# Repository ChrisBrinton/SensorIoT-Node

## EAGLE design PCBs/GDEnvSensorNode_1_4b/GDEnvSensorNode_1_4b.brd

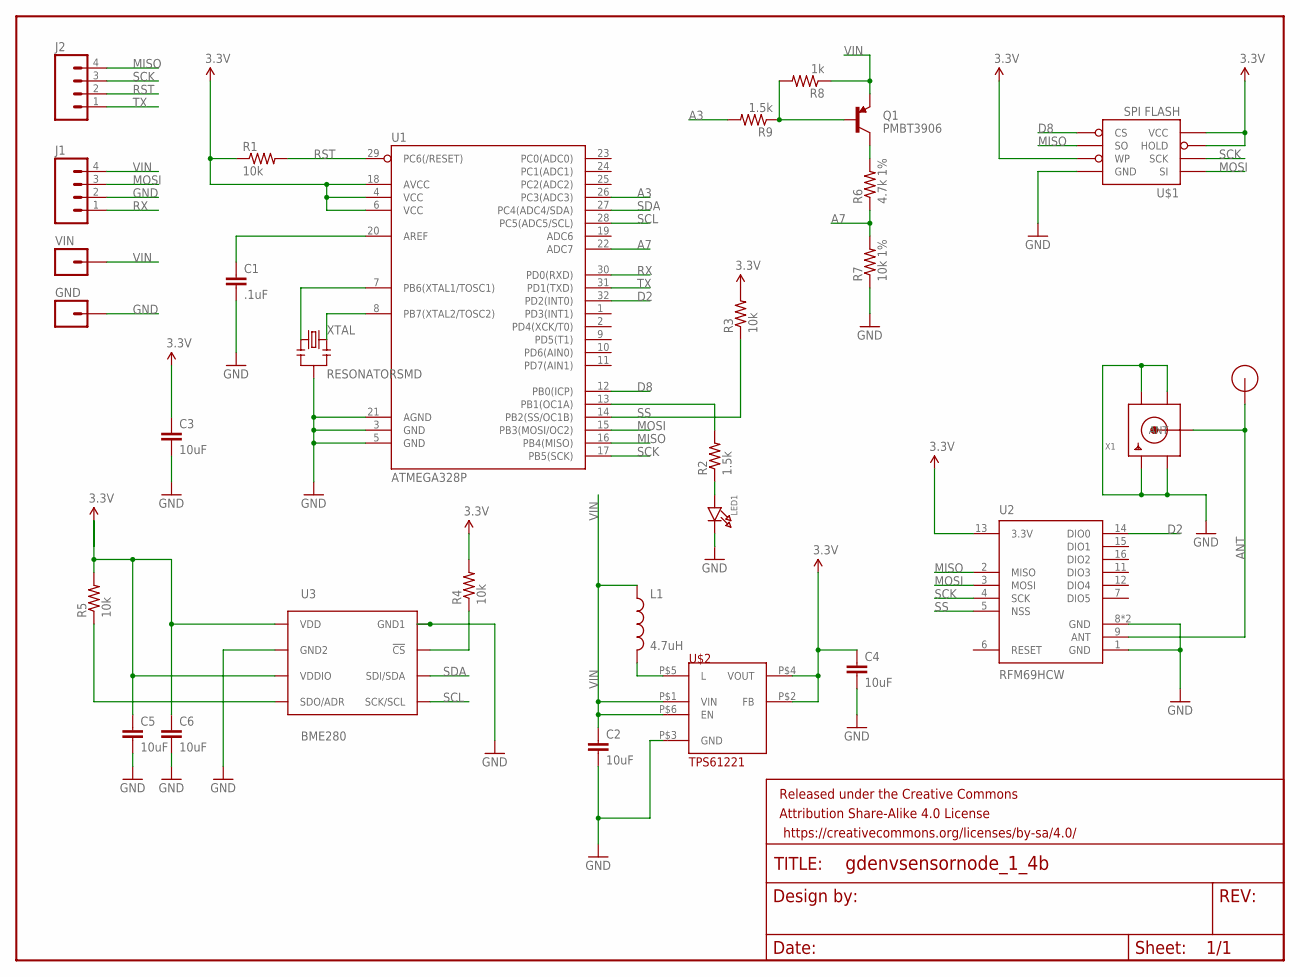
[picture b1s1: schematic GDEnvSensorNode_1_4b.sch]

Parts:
C1: .1uF; 0805
C2, C3, C4, C5, C6: 10uF; 0805
FRAME1: FRAME-LETTER; CREATIVE_COMMONS
GND: M01PTH_2MM; 1X01_2MM
J1, J2: M04PTH; 1X04
L1: 4.7uH; 1210
LED1: LED0805; CHIPLED_0805
Q1: PMBT3906; SOT23-3
R1, R3, R4, R5: 10k; 0805
R2, R9: 1.5k; 0805
R6: 4.7k 1%; 0805
R7: 10k 1%; 0805
R8: 1k; 0805
U1: ATMEGA328P; TQFP32-08
U2: RFM69HCW; RFM69HCW-XXXS2
U3: BME280; BME280_LGA
U$1: SPI FLASH; SO08
U$2: TPS61221
U$4: RFM12B_ANTENNA; RFM12B-ANTENNA
VIN: M01PTH_2MM; 1X01_2MM
X1: SMACONNECTOR_EDGE_UFL; SMA_EDGELAUNCH_UFL
XTAL: RESONATORSMD; RESONATOR-SMD

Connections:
3.3V: C3.1, C4.1, R1.1, R3.2, R4.2, U1.4 (VCC), U1.6 (VCC), U1.18 (AVCC), U2.13 (3.3V), U$1.3_WP (WP), U$1.7_HOLD (HOLD), U$1.8_VCC (VCC), U$2.P$2 (FB), U$2.P$4 (VOUT)
A3: R9.2, U1.26 (PC3(ADC3))
A7: R6.1, R7.2, U1.22 (ADC7)
ANT: U2.9 (ANT), U$4.P$1, X1.P (ANT)
D2: U1.32 (PD2(INT0)), U2.14 (DIO0)
D8: U1.12 (PB0(ICP)), U$1.1_CS (CS)
GND: C1.2, C2.2, C3.2, C4.2, C5.2, C6.2, GND.1, J1.2, LED1.C, R7.1, U1.3 (GND), U1.5 (GND), U1.21 (AGND), U2.1 (GND), U2.8 (GND), U2.10 (GND), U3.P$1 (GND1), U3.P$7 (GND2), U$1.4_GND (GND), U$2.P$3 (GND), X1.GND@1 (GND1), X1.GND@2 (GND2), X1.GND@3 (GND3), X1.GND@4 (GND4), XTAL.2
L: L1.2, U$2.P$5 (L)
MISO: J2.4, U1.16 (PB4(MISO)), U2.2 (MISO), U$1.2_SO (SO)
MOSI: J1.3, U1.15 (PB3(MOSI/OC2)), U2.3 (MOSI), U$1.5_SI (SI)
unnamed: U1.8 (PB7(XTAL2/TOSC2)), XTAL.3
unnamed: U1.7 (PB6(XTAL1/TOSC1)), XTAL.1
unnamed: LED1.A, R2.1
unnamed: Q1.3 (C), R6.2
unnamed: R4.1, U3.P$2 (!CS)
unnamed: Q1.1 (B), R8.2, R9.1
unnamed: R2.2, U1.13 (PB1(OC1A))
unnamed: C1.1, U1.20 (AREF)
unnamed: C5.1, C6.1, R5.2, U3.P$6 (VDDIO), U3.P$8 (VDD)
unnamed: R5.1, U3.P$5 (SDO/ADR)
RST: J2.2, R1.2, U1.29 (PC6(/RESET))
RX: J1.1, U1.30 (PD0(RXD))
SCK: J2.3, U1.17 (PB5(SCK)), U2.4 (SCK), U$1.6_SCK (SCK)
SCL: U1.28 (PC5(ADC5/SCL)), U3.P$4 (SCK/SCL)
SDA: U1.27 (PC4(ADC4/SDA)), U3.P$3 (SDI/SDA)
SS: R3.1, U1.14 (PB2(SS/OC1B)), U2.5 (NSS)
TX: J2.1, U1.31 (PD1(TXD))
VIN: C2.1, J1.4, L1.1, Q1.2 (E), R8.1, U$2.P$1 (VIN), U$2.P$6 (EN), VIN.1

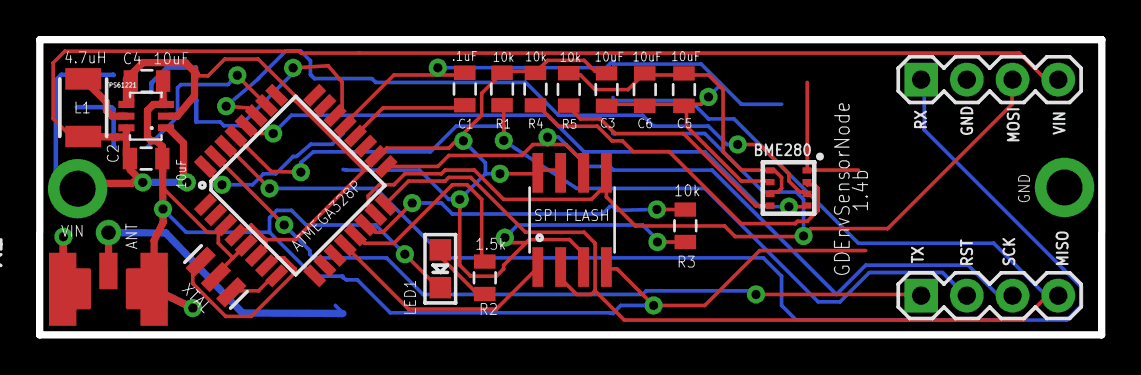
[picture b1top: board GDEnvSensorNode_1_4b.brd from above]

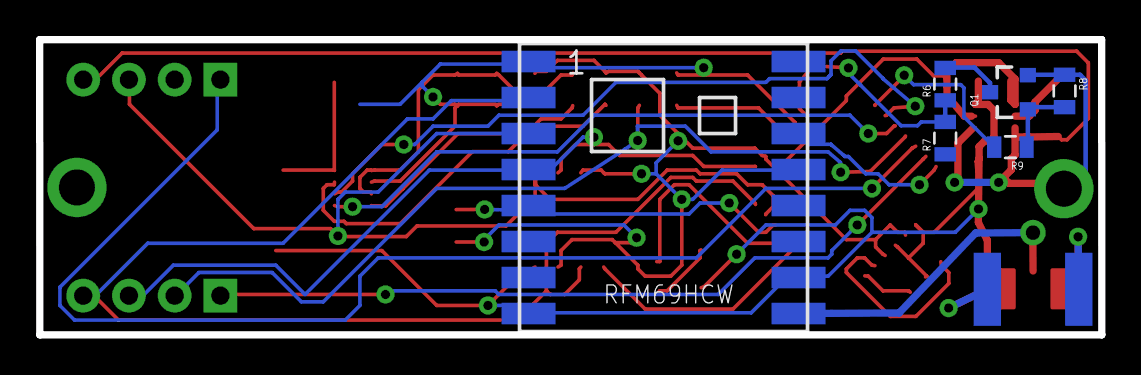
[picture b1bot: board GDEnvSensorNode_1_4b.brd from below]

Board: 2 copper layers, 59.0 x 16.4 mm, 31 parts (6 on the bottom side), 28 nets.

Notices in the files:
parts and their libraries:
SparkFun-Capacitors: Licensing: Creative Commons ShareAlike 4.0 International - https://creativecommons.org/licenses/by-sa/4.0
SparkFun-Aesthetics: Released under the Creative Commons Attribution Share-Alike 4.0 License
SparkFun-Aesthetics: https://creativecommons.org/licenses/by-sa/4.0
